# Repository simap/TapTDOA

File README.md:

TapTDOA
===============

TapTDOA is a project to explore the possibility of making a generic tap interface controller. 

[See Hackaday project for details](https://hackaday.io/project/159821-taptdoa)

License
===============

Portions of the code are provided by third parties, see below for licensing information for those portions. This includes the ARM Math and DSP library as well as STM drivers and HAL code used for setting up the microcontroller.

The MIT License

Copyright (c) 2018 Ben Hencke

Permission is hereby granted, free of charge, to any person obtaining a copy
of this software and associated documentation files (the "Software"), to deal
in the Software without restriction, including without limitation the rights
to use, copy, modify, merge, publish, distribute, sublicense, and/or sell
copies of the Software, and to permit persons to whom the Software is
furnished to do so, subject to the following conditions:

The above copyright notice and this permission notice shall be included in all
copies or substantial portions of the Software.

THE SOFTWARE IS PROVIDED "AS IS", WITHOUT WARRANTY OF ANY KIND, EXPRESS OR
IMPLIED, INCLUDING BUT NOT LIMITED TO THE WARRANTIES OF MERCHANTABILITY,
FITNESS FOR A PARTICULAR PURPOSE AND NONINFRINGEMENT. IN NO EVENT SHALL THE
AUTHORS OR COPYRIGHT HOLDERS BE LIABLE FOR ANY CLAIM, DAMAGES OR OTHER
LIABILITY, WHETHER IN AN ACTION OF CONTRACT, TORT OR OTHERWISE, ARISING FROM,
OUT OF OR IN CONNECTION WITH THE SOFTWARE OR THE USE OR OTHER DEALINGS IN THE
SOFTWARE.

----------

Portions of code are provided by ARM Limited and have the following license:

    Copyright (C) 2010-2015 ARM Limited. All rights reserved.

    $Date:        20. October 2015
    $Revision:    V1.4.5 b

    Project:      CMSIS DSP Library
    Title:        arm_math.h

    Description:  Public header file for CMSIS DSP Library

    Target Processor: Cortex-M7/Cortex-M4/Cortex-M3/Cortex-M0

    Redistribution and use in source and binary forms, with or without
    modification, are permitted provided that the following conditions
    are met:
     - Redistributions of source code must retain the above copyright
       notice, this list of conditions and the following disclaimer.
     - Redistributions in binary form must reproduce the above copyright
       notice, this list of conditions and the following disclaimer in
       the documentation and/or other materials provided with the
       distribution.
     - Neither the name of ARM LIMITED nor the names of its contributors
       may be used to endorse or promote products derived from this
       software without specific prior written permission.

    THIS SOFTWARE IS PROVIDED BY THE COPYRIGHT HOLDERS AND CONTRIBUTORS
    "AS IS" AND ANY EXPRESS OR IMPLIED WARRANTIES, INCLUDING, BUT NOT
    LIMITED TO, THE IMPLIED WARRANTIES OF MERCHANTABILITY AND FITNESS
    FOR A PARTICULAR PURPOSE ARE DISCLAIMED. IN NO EVENT SHALL THE
    COPYRIGHT OWNER OR CONTRIBUTORS BE LIABLE FOR ANY DIRECT, INDIRECT,
    INCIDENTAL, SPECIAL, EXEMPLARY, OR CONSEQUENTIAL DAMAGES (INCLUDING,
    BUT NOT LIMITED TO, PROCUREMENT OF SUBSTITUTE GOODS OR SERVICES;
    LOSS OF USE, DATA, OR PROFITS; OR BUSINESS INTERRUPTION) HOWEVER
    CAUSED AND ON ANY THEORY OF LIABILITY, WHETHER IN CONTRACT, STRICT
    LIABILITY, OR TORT (INCLUDING NEGLIGENCE OR OTHERWISE) ARISING IN
    ANY WAY OUT OF THE USE OF THIS SOFTWARE, EVEN IF ADVISED OF THE
    POSSIBILITY OF SUCH DAMAGE.

---------

Portions of code are provided by STMicroelectronics International N.V. and have the following license:

    Copyright (c) 2018 STMicroelectronics International N.V. 
    All rights reserved.

    Redistribution and use in source and binary forms, with or without 
    modification, are permitted, provided that the following conditions are met:

    1. Redistribution of source code must retain the above copyright notice, 
      this list of conditions and the following disclaimer.
    2. Redistributions in binary form must reproduce the above copyright notice,
      this list of conditions and the following disclaimer in the documentation
      and/or other materials provided with the distribution.
    3. Neither the name of STMicroelectronics nor the names of other 
      contributors to this software may be used to endorse or promote products 
      derived from this software without specific written permission.
    4. This software, including modifications and/or derivative works of this 
      software, must execute solely and exclusively on microcontroller or
      microprocessor devices manufactured by or for STMicroelectronics.
    5. Redistribution and use of this software other than as permitted under 
      this license is void and will automatically terminate your rights under 
      this license. 

    THIS SOFTWARE IS PROVIDED BY STMICROELECTRONICS AND CONTRIBUTORS "AS IS" 
    AND ANY EXPRESS, IMPLIED OR STATUTORY WARRANTIES, INCLUDING, BUT NOT 
    LIMITED TO, THE IMPLIED WARRANTIES OF MERCHANTABILITY, FITNESS FOR A 
    PARTICULAR PURPOSE AND NON-INFRINGEMENT OF THIRD PARTY INTELLECTUAL PROPERTY
    RIGHTS ARE DISCLAIMED TO THE FULLEST EXTENT PERMITTED BY LAW. IN NO EVENT 
    SHALL STMICROELECTRONICS OR CONTRIBUTORS BE LIABLE FOR ANY DIRECT, INDIRECT,
    INCIDENTAL, SPECIAL, EXEMPLARY, OR CONSEQUENTIAL DAMAGES (INCLUDING, BUT NOT
    LIMITED TO, PROCUREMENT OF SUBSTITUTE GOODS OR SERVICES; LOSS OF USE, DATA, 
    OR PROFITS; OR BUSINESS INTERRUPTION) HOWEVER CAUSED AND ON ANY THEORY OF 
    LIABILITY, WHETHER IN CONTRACT, STRICT LIABILITY, OR TORT (INCLUDING 
    NEGLIGENCE OR OTHERWISE) ARISING IN ANY WAY OUT OF THE USE OF THIS SOFTWARE,
    EVEN IF ADVISED OF THE POSSIBILITY OF SUCH DAMAGE.

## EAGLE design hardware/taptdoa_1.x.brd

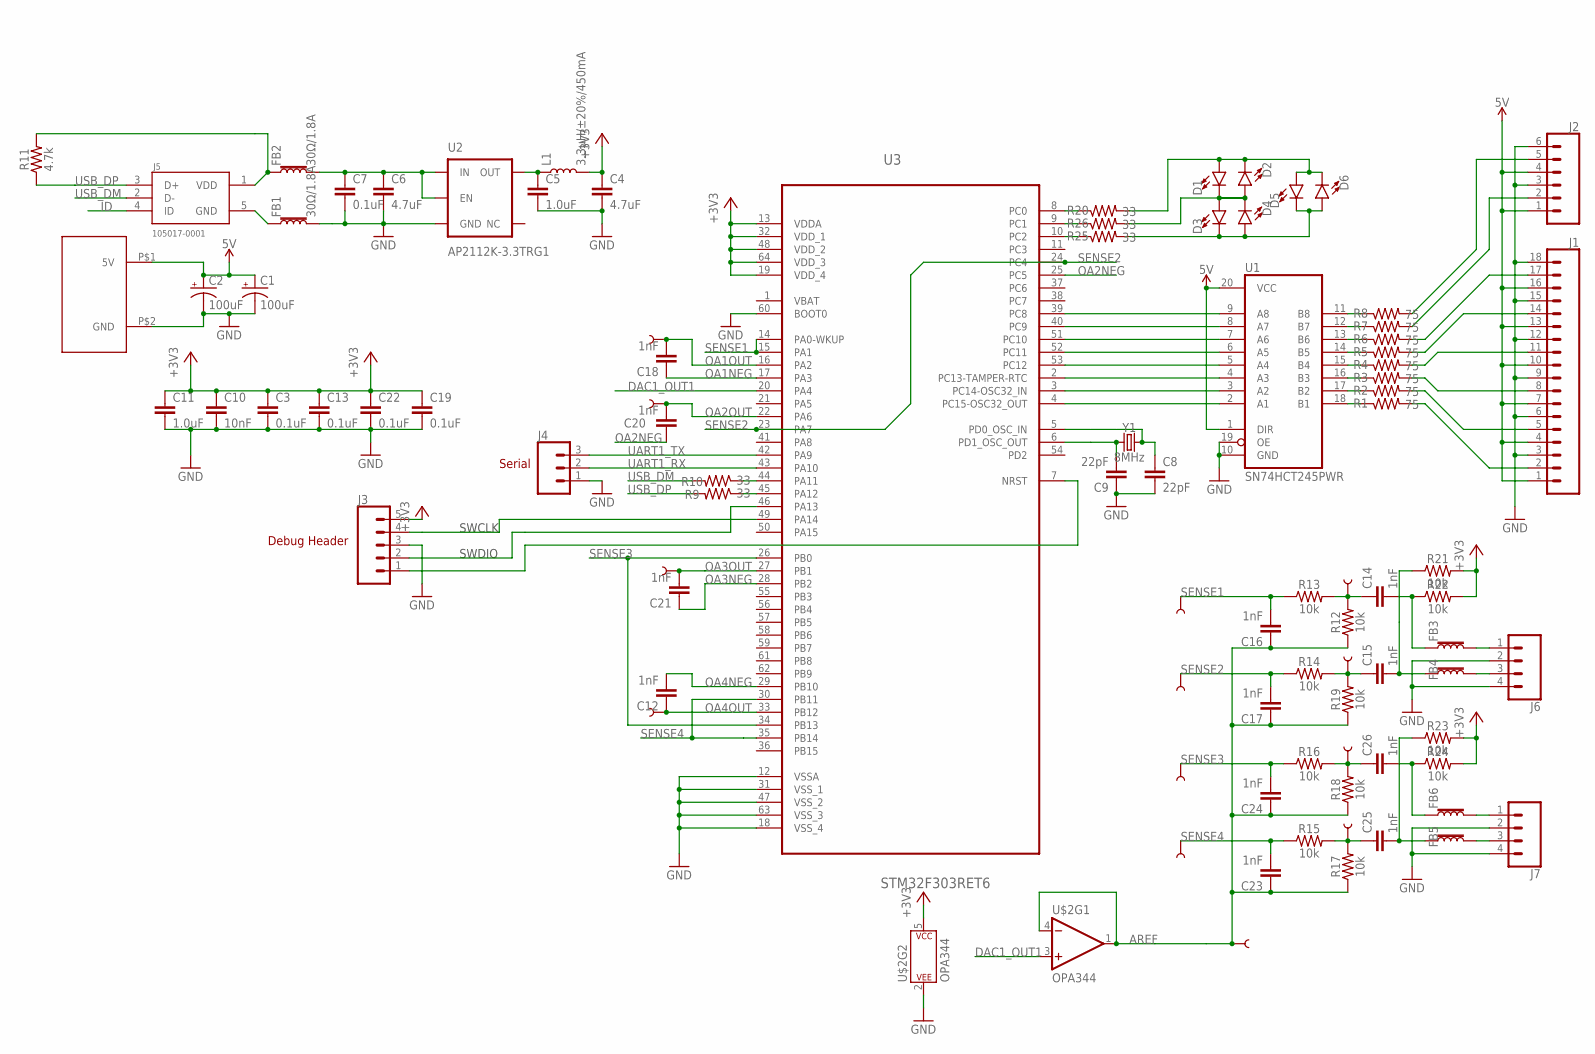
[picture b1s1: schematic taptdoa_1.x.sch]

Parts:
C1, C2: 100uF; PANASONIC_D
C3, C7, C13, C19, C22: 0.1uF; 0603
C4, C6: 4.7uF; 0603
C5, C11: 1.0uF; 0603
C8, C9: 22pF; 0603
C10: 10nF; 0603
C12, C14, C15, C16, C17, C18, C20, C21, C23, C24, C25, C26: 1nF; 0603
D1, D2, D3, D4, D5, D6: LED0603; LED-0603
FB1, FB2, FB3, FB4, FB5, FB6: 30Ω/1.8A; 0603
J1: CONN_18; 1X18
J2: CONN_06LOCK; 1X06_LOCK
J3: CONN_05LOCK; 1X05_LOCK
J4: CONN_03; 1X03
J5: 105017-0001; MOLEX_105017-0001
J6, J7: CONN_04LOCK_LONGPADS; 1X04_LOCK_LONGPADS
L1: 3.3µH/±20%/450mA; 0805
R1, R2, R3, R4, R5, R6, R7, R8: 75; 0603
R9, R10, R20, R25, R26: 33; 0603
R11: 4.7k; 0603
R12, R13, R14, R15, R16, R17, R18, R19, R21, R22, R23, R24: 10k; 0603
TP1, TP2, TP3, TP4, TP5, TP6, TP7, TP8, TP9, TP10, TP11, TP12, TP13: TEST-POINT3X4; PAD.03X.04
U1: SN74HCT245PWR; TSSOP20
U2: AP2112K-3.3TRG1; SOT23-5
U3: STM32F303RET6; QFP50P1200X1200X160-64N
U$1: XT30XT30_THRUHOLE; ZT30
U$2: OPA344; SOT23-5
Y1: 8MHz; HC49UP

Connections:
5V: C1.+, C2.+, J1.1, J1.4, J1.7, J1.10, J1.13, J1.16, J2.1, J2.4, U1.1 (DIR), U1.20 (VCC), U$1.P$1 (5V)
+3V3: C3.1, C4.1, C10.1, C11.1, C13.1, C19.1, C22.1, J3.5, L1.2, R21.2, R22.2, R23.2, R24.2, U3.13 (VDDA), U3.19 (VDD_4), U3.32 (VDD_1), U3.48 (VDD_2), U3.64 (VDD_3), U$2.5 (P$V+)
AREF: C16.1, C17.1, C23.1, C24.1, R12.1, R17.1, R18.1, R19.1, TP8.P$1, U$2.1 (OUT), U$2.4 (-IN)
DAC1_OUT1: U3.20 (PA4), U$2.3 (+IN)
GND: C1.-, C2.-, C3.2, C4.2, C5.2, C6.2, C7.2, C8.2, C9.1, C10.2, C11.2, C13.2, C19.2, C22.2, FB1.2, J1.3, J1.6, J1.9, J1.12, J1.15, J1.18, J2.3, J2.6, J3.3, J4.1, J6.2, J6.4, J7.2, J7.4, U1.10 (GND), U1.19 (OE), U2.2 (GND), U3.12 (VSSA), U3.18 (VSS_4), U3.31 (VSS_1), U3.47 (VSS_2), U3.60 (BOOT0), U3.63 (VSS_3), U$1.P$2 (GND), U$2.2 (P$V-)
HP1: C14.1, R12.2, R13.2, TP2.P$1
HP2: C15.1, R14.2, R19.2, TP3.P$1
HP3: C26.1, R16.2, R18.2, TP12.P$1
HP4: C25.1, R15.2, R17.2, TP13.P$1
ID: J5.4 (ID)
LED0: J1.2, R1.2
LED1: J1.5, R2.2
LED2: J1.8, R3.2
LED3: J1.11, R4.2
LED4: J1.14, R5.2
LED5: J1.17, R6.2
unnamed: R20.1, U3.8 (PC0)
unnamed: D1.A, D2.C, D5.A, D6.C, R20.2
unnamed: R25.1, U3.10 (PC2)
unnamed: R26.1, U3.9 (PC1)
unnamed: D1.C, D2.A, D3.A, D4.C, R26.2
unnamed: R10.1, U3.44 (PA11)
unnamed: R9.1, U3.45 (PA12)
unnamed: FB1.1, J5.5 (GND)
unnamed: C5.1, L1.1, U2.5 (OUT)
unnamed: R1.1, U1.18 (B1)
unnamed: R2.1, U1.17 (B2)
unnamed: R3.1, U1.16 (B3)
unnamed: R4.1, U1.15 (B4)
unnamed: R5.1, U1.14 (B5)
unnamed: R6.1, U1.13 (B6)
unnamed: C14.2, FB3.1, R22.1
unnamed: C26.2, FB6.1, R24.1
unnamed: C15.2, FB4.1, R21.1
unnamed: D3.C, D4.A, D5.C, D6.A, R25.2
unnamed: C25.2, FB5.1, R23.1
unnamed: R7.1, U1.12 (B7)
unnamed: R8.1, U1.11 (B8)
unnamed: J2.2, R7.2
unnamed: J2.5, R8.2
unnamed: FB3.2, J6.1
unnamed: FB6.2, J7.1
unnamed: FB5.2, J7.3
unnamed: FB4.2, J6.3
NRST: J3.1, U3.7 (NRST)
OA1NEG: C18.1, U3.17 (PA3)
OA1OUT: C18.2, TP6.P$1, U3.16 (PA2)
OA2NEG: C20.1, U3.25 (PC5)
OA2OUT: C20.2, TP7.P$1, U3.22 (PA6)
OA3NEG: C21.1, U3.28 (PB2)
OA3OUT: C21.2, TP9.P$1, U3.27 (PB1)
OA4NEG: C12.2, U3.29 (PB10)
OA4OUT: C12.1, TP1.P$1, U3.33 (PB12)
PA13: J3.2, U3.46 (PA13)
PA14: J3.4, U3.49 (PA14)
PC8: U1.9 (A8), U3.39 (PC8)
PC9: U1.8 (A7), U3.40 (PC9)
PC10: U1.7 (A6), U3.51 (PC10)
PC11: U1.6 (A5), U3.52 (PC11)
PC12: U1.5 (A4), U3.53 (PC12)
PC13: U1.4 (A3), U3.2 (PC13-TAMPER-RTC)
PC14: U1.3 (A2), U3.3 (PC14-OSC32_IN)
PC15: U1.2 (A1), U3.4 (PC15-OSC32_OUT)
PD0_OSC_IN: C8.1, U3.5 (PD0_OSC_IN), Y1.2
PD1_OSC_OUT: C9.2, U3.6 (PD1_OSC_OUT), Y1.1
SENSE1: C16.2, R13.1, TP4.P$1, U3.14 (PA0-WKUP), U3.15 (PA1)
SENSE2: C17.2, R14.1, TP5.P$1, U3.23 (PA7), U3.24 (PC4)
SENSE3: C24.2, R16.1, TP10.P$1, U3.26 (PB0), U3.34 (PB13)
SENSE4: C23.2, R15.1, TP11.P$1, U3.30 (PB11), U3.35 (PB14)
UART1_RX: J4.2, U3.43 (PA10)
UART1_TX: J4.3, U3.42 (PA9)
USB_DM: J5.2 (D-), R10.2
USB_DP: J5.3 (D+), R9.2, R11.1
VUSB: FB2.1, J5.1 (VDD), R11.2
VUSB2: C6.1, C7.1, FB2.2, U2.1 (IN), U2.3 (EN)

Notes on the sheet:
SWDIO
SWCLK
Debug Header
Serial

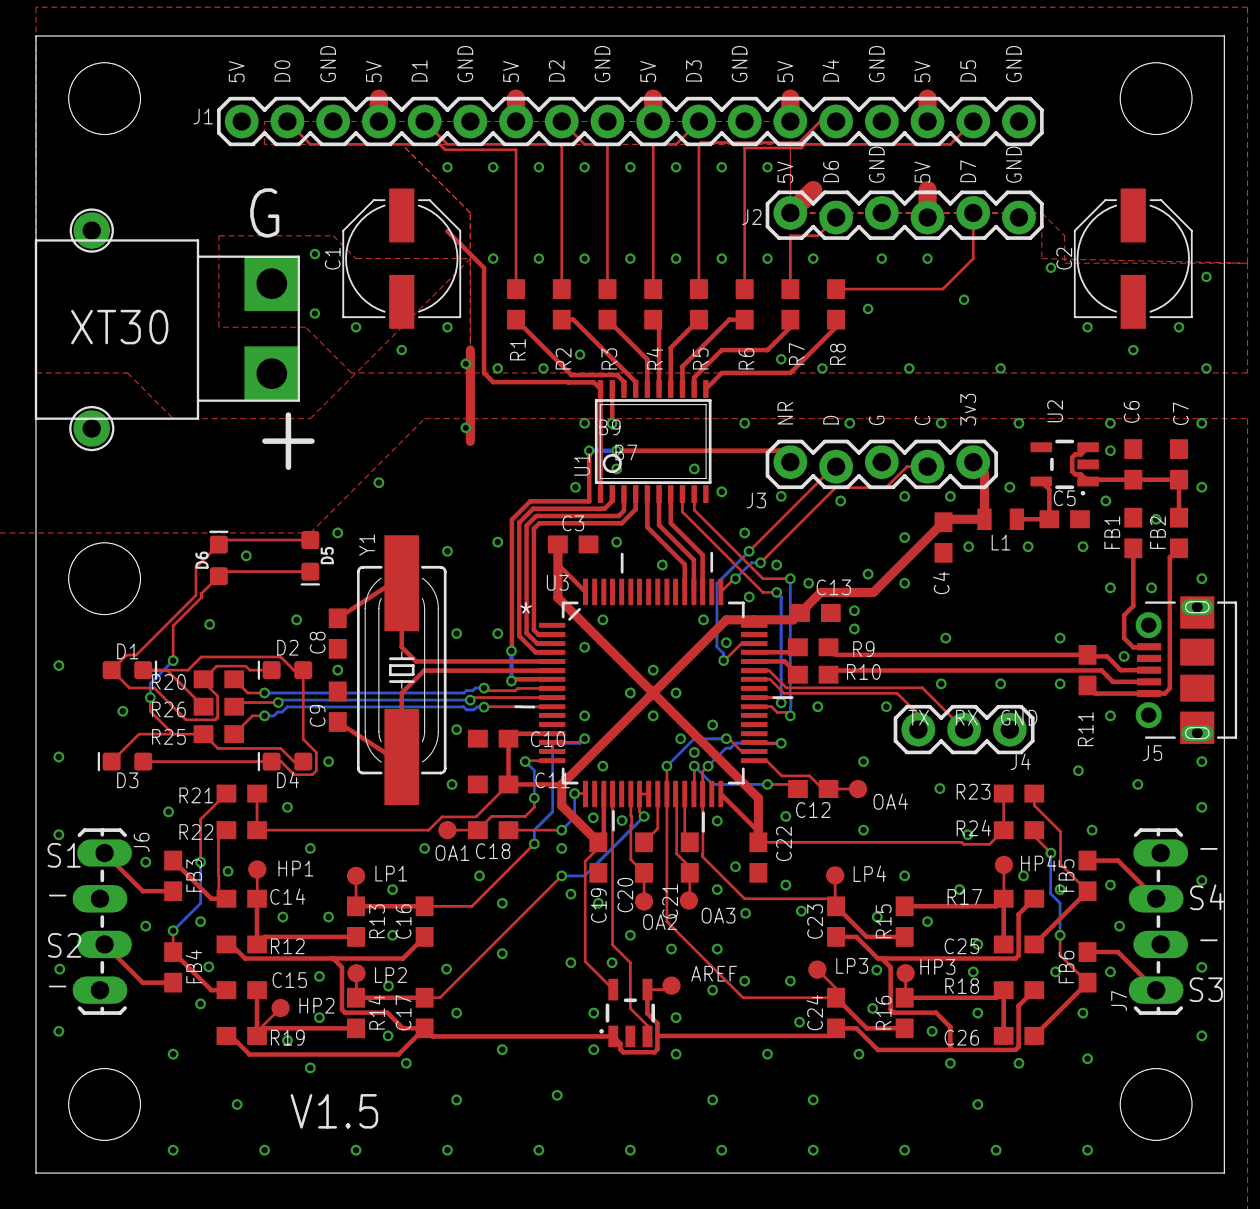
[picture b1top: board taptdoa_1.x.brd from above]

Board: 2 copper layers, 66.0 x 63.2 mm, 91 parts (0 on the bottom side), 74 nets.

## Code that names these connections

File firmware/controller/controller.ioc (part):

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Mcu.Name=STM32F303R(D-E)Tx
Mcu.Package=LQFP64
Mcu.UserName=STM32F303RETx
PA0.Mode=IN1-Single-Ended
PA0.Signal=ADC1_IN1
PA1.Mode=PGA Connected
PA1.Signal=OPAMP1_VINP
PA10.GPIOParameters=GPIO_Label
PA10.GPIO_Label=uartRx
PA10.Mode=Asynchronous
PA10.Signal=USART1_RX
PA11.Mode=Device
PA11.Signal=USB_DM
PA12.Mode=Device
PA12.Signal=USB_DP
PA13.Mode=Serial_Wire
PA13.Signal=SYS_JTMS-SWDIO
PA14.Mode=Serial_Wire
PA14.Signal=SYS_JTCK-SWCLK
PA2.Mode=PGA Connected
PA2.Signal=OPAMP1_VOUT
PA3.Mode=PGA Connected
PA3.Signal=OPAMP1_VINM
PA4.Signal=COMP_DAC11_group
PA5.Signal=COMP_DAC12_group
PA6.GPIOParameters=GPIO_Mode
PA6.GPIO_Mode=GPIO_MODE_ANALOG
PA6.Mode=PGA Connected
PA6.Signal=OPAMP2_VOUT
PA7.Mode=PGA Connected
PA7.Signal=OPAMP2_VINP
PA9.GPIOParameters=GPIO_Label
PA9.GPIO_Label=uartTx
PA9.Mode=Asynchronous
PA9.Signal=USART1_TX
PB0.Mode=PGA Connected
PB0.Signal=OPAMP3_VINP
PB1.Mode=PGA Connected
PB1.Signal=OPAMP3_VOUT
PB10.Mode=PGA Connected
PB10.Signal=OPAMP4_VINM
PB11.Mode=PGA Connected
PB11.Signal=OPAMP4_VINP
PB12.Mode=PGA Connected
PB12.Signal=OPAMP4_VOUT
PB13.Mode=IN5-Single-Ended
PB13.Signal=ADC3_IN5
PB14.Mode=IN4-Single-Ended
PB14.Signal=ADC4_IN4
PB2.Mode=PGA Connected
PB2.Signal=OPAMP3_VINM
PC0.Signal=S_TIM1_CH1
PC1.Signal=S_TIM1_CH2
PC10.Signal=GPIO_Output
PC11.Signal=GPIO_Output
PC12.Signal=GPIO_Output
PC13.Signal=GPIO_Output
PC14-OSC32_IN.Signal=GPIO_Output
PC15-OSC32_OUT.Signal=GPIO_Output
PC4.Mode=IN5-Single-Ended
PC4.Signal=ADC2_IN5
PC5.Mode=PGA Connected
PC5.Signal=OPAMP2_VINM
PC8.Signal=GPIO_Output
PC9.Signal=GPIO_Output
PF0-OSC_IN.Mode=HSE-External-Oscillator
PF0-OSC_IN.Signal=RCC_OSC_IN
PF1-OSC_OUT.Mode=HSE-External-Oscillator
PF1-OSC_OUT.Signal=RCC_OSC_OUT
RCC.HSE_VALUE=8000000
RCC.SYSCLKFreq_VALUE=72000000
RCC.SYSCLKSourceVirtual=RCC_SYSCLKSOURCE_PLLCLK
board=controller

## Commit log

2018-08-06 initial
    set up all the peripherals
    trigger on ADC WD
    start timer to capture some following data
    spit out raw data over usb serial console
    boards with some fixes
2018-08-06 readme
2018-08-26 WIP large FIR + xcorr. takes 1.8s, iffy
2018-08-26 WIP this version finds 20khz signals pretty well and fast
2018-08-27 v1.2 of board
2018-08-27 license
2018-09-18 working on LEDs, simple threshold detection for now, limited filtering
2018-09-18 add eclipse project file
2018-09-18 cdt project file
2018-09-18 need cdt project files
2018-10-01 new line method
2018-10-12 better debug, dynamic threshold
2018-10-16 re layout board
2018-10-16 cleanup renumber
2018-10-16 update code for new board rev
    move led data to port c
    extra analog channels
    sampling time
2018-10-19 ws2812 timer
2018-10-31 dump raw data as hex as fast as possible
2018-11-06 fix circular buffer dump, led timing
2018-11-08 bump gain to 4x, more debug data
2018-11-10 backup algos, auto mean
2018-11-10 50khz sample, 2khz target. more debug data
2018-11-10 turn off raw data dumps
2018-11-27 new board rev with leds, fix swd pins
2018-11-27 better fallback algo
2019-01-11 more LEDs
2019-01-11 threshold tweaks
2019-01-11 fix minor drc

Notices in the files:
parts and their libraries:
SparkFun-Clocks: Licensing: Creative Commons ShareAlike 4.0 International - https://creativecommons.org/licenses/by-sa/4.0
